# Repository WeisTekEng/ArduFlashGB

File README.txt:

I created this repo to help document my personal experiance in creating a GB flash card hearby called ArduFlashGB (name not will most likey change.)
More will be updated soon.

These are good links for information regarding this project.
Digital-Circuitry:
http://www.digital-circuitry.com/GameBoy.htm

InsideGadgets Blog:
https://www.insidegadgets.com/2011/03/19/gbcartread-arduino-based-gameboy-cart-reader-%E2%80%93-part-1-read-the-rom/
https://www.insidegadgets.com/2011/03/28/gbcartread-arduino-based-gameboy-cart-reader-%E2%80%93-part-2-read-the-ram/
https://www.insidegadgets.com/2011/04/07/gbcartread-arduino-based-gameboy-cart-reader-%E2%80%93-part-3-write-to-ram/

Jazz Disassemblies Blog:
http://jazz-disassemblies.blogspot.com/2013/10/gameboy-mbc-which-to-choose.html

Everything you always wanted to know about GAMEBOY: (in pdf format in documents folder)
http://www.devrs.com/gb/files/gbspec.txt

Post by xzakox on Chipmusic.org forums:
http://chipmusic.org/forums/topic/2988/mbc5-clone-in-cpld/

reinerziegler's blog:
http://reinerziegler.de/readplus.htm#GB_Flasher

Marc Rawer's Blog:
http://marc.rawer.de/Gameboy/

Dillon Nichol's Blog: (he has his carts for sale on Tindi)
http://tinkeringetc.blogspot.com/p/homebrew-gameboy-cartridge.html

MBC-5 CPLD blog:
http://home1.stofanet.dk/hvaba/gameboy/mbc5cpld/

qwertymodo's Posts about his CPLD based cart on Nesdev forums:
http://forums.nesdev.com/viewtopic.php?f=20&t=9443&sid=6d7f7b9e4511b7dcb22689f2313be0eb

Another post by xzackx on chipmusic forums
http://chipmusic.org/forums/topic/2988/mbc5-clone-in-cpld/

Wiki artical about the MBC-5 memory controller:
http://gbdev.gg8.se/wiki/articles/MBC5

gitourious.org c code implimentation of a MBC-5 Memory controller:
https://gitorious.org/bgameboy/bgameboy/source/a7ffbd784b9f59d248df8e680ae4e8cc5543308b:gameboy/cartridge/mbc5/mbc5.cpp

pastebin.com VHDL code implimentation of an MBC-5 (Unfinished?)
http://pastebin.com/c1SyhLEn

Game Boy & Nintendo are trademarks 
of Nintendo Co., Ltd. of Kyoto, Japan.

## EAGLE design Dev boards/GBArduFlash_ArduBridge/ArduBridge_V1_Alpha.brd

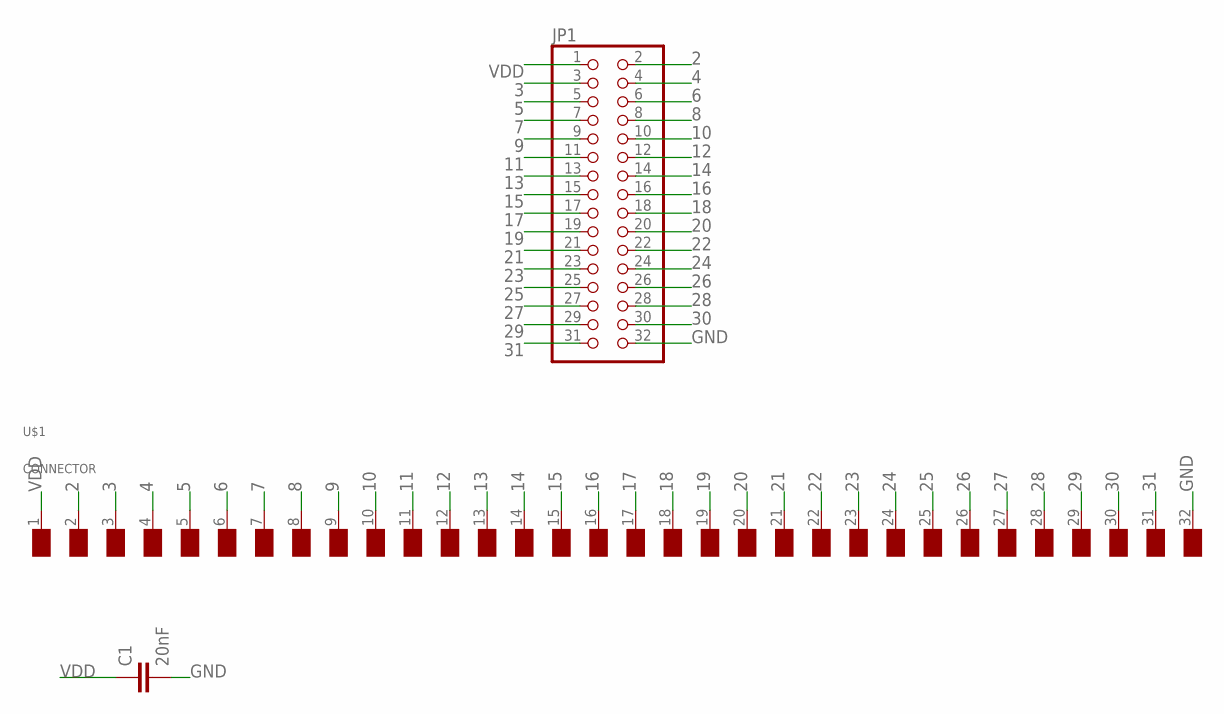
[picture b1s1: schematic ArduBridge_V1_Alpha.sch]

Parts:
C1: 20nF; C0805
JP1: PINHD-2X16/90; 2X16/90
U$1: CONNECTOR

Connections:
2: JP1.2, U$1.2 (NC)
3: JP1.3, U$1.3 (/WR)
4: JP1.4, U$1.4 (/RD)
5: JP1.5, U$1.5 (/RCS)
6: JP1.6, U$1.6 (A0)
7: JP1.7, U$1.7 (A1)
8: JP1.8, U$1.8 (A2)
9: JP1.9, U$1.9 (A3)
10: JP1.10, U$1.10 (A4)
11: JP1.11, U$1.11 (A5)
12: JP1.12, U$1.12 (A6)
13: JP1.13, U$1.13 (A7)
14: JP1.14, U$1.14 (A8)
15: JP1.15, U$1.15 (A9)
16: JP1.16, U$1.16 (A10)
17: JP1.17, U$1.17 (A11)
18: JP1.18, U$1.18 (A12)
19: JP1.19, U$1.19 (A13)
20: JP1.20, U$1.20 (A14)
21: JP1.21, U$1.21 (A15)
22: JP1.22, U$1.22 (D0)
23: JP1.23, U$1.23 (D1)
24: JP1.24, U$1.24 (D2)
25: JP1.25, U$1.25 (D3)
26: JP1.26, U$1.26 (D4)
27: JP1.27, U$1.27 (D5)
28: JP1.28, U$1.28 (D6)
29: JP1.29, U$1.29 (D7)
30: JP1.30, U$1.30 (/RS)
31: JP1.31, U$1.31 (VIN)
GND: C1.2, JP1.32, U$1.32 (GND)
VDD: C1.1, JP1.1, U$1.1 (VDD)

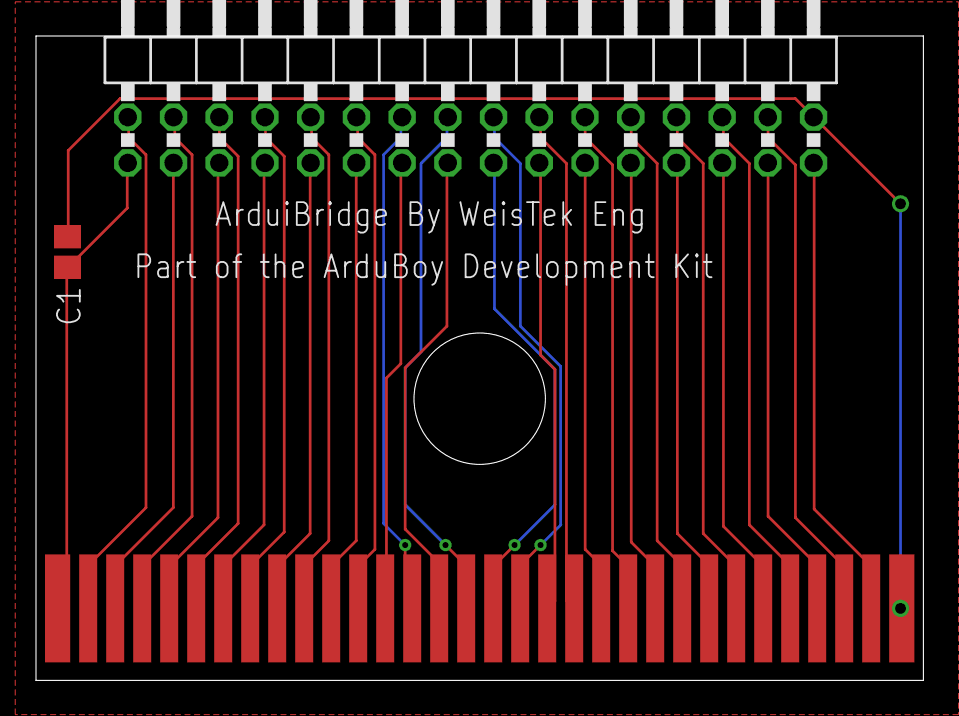
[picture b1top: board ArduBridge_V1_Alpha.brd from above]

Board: 2 copper layers, 49.3 x 35.8 mm, 3 parts (0 on the bottom side), 32 nets.

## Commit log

2014-12-24 :boom::camel: Added .gitattributes
2014-12-24 First Upload.
    Some important information I have found on the internet, none of this is
    my personal work except the eagle design files present in ArduBridge
    folder. More will be added soon.
2014-12-24 Fixed readme
2014-12-24 Added photo of ArduBridge
    ArduBridge is a connection from a GB to anything you wish to connect it
    to.
2014-12-24 Updated Readme
    I have updated the readme to include useful links I have found on the
    web, if anyone who owns the content to these links wish's I take them
    out of the readme please let me know.
2014-12-28 Cleaned repo, added gbshooper by David Pello
    Cleaned up the repo, added David Pello's gbshooper (GB cart flasher)
    program, attached a copy of Open GPLv3.
